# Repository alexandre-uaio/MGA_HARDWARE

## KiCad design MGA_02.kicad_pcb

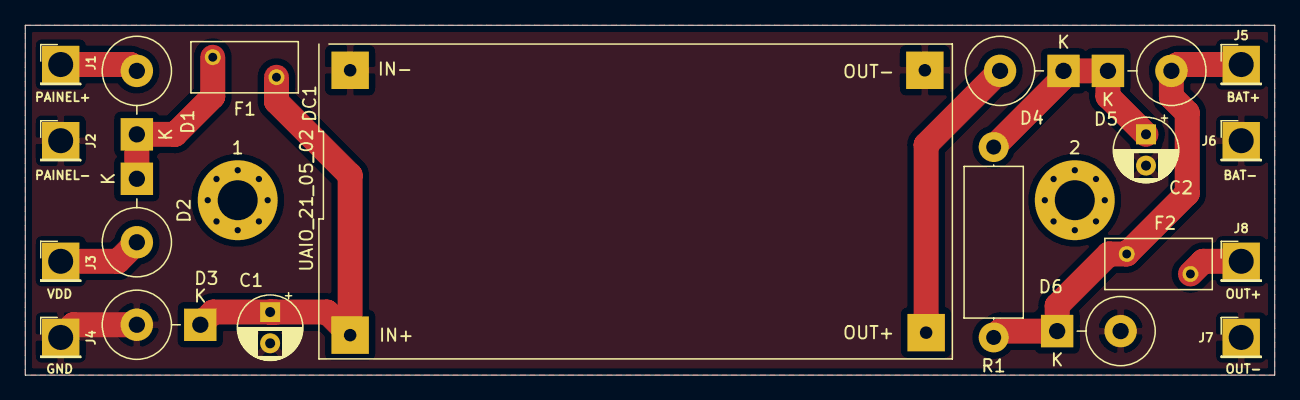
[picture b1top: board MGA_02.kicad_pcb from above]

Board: 2 copper layers, 100.0 x 28.0 mm, 22 parts (0 on the bottom side), 9 nets.

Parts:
1, 2: MountingHole_3.2mm_M3_Pad_Via
C1, C2: 100uFx50V; CP_Radial_D5.0mm_P2.50mm
D1, D2, D3, D4, D5, D6: UF5406; D_DO-201AE_P5.08mm_Vertical_KathodeUp
DC1: DC_DC_60V
F1, F2: Polyfuse; Fuse_BelFuse_0ZRE0005FF_L8.3mm_W3.8mm
J1: Painel +; PinHeader_1x01_F_2mm
J2: Painel -; PinHeader_1x01_F_2mm
J3: VDD; PinHeader_1x01_F_2mm
J4: GND; PinHeader_1x01_F_2mm
J5: BAT +; PinHeader_1x01_F_2mm
J6: BAT -; PinHeader_1x01_F_2mm
J7: OUT-; PinHeader_1x01_F_2mm
J8: OUT+; PinHeader_1x01_F_2mm
R1: 10R/3W; R_Axial_DIN0414_L11.9mm_D4.5mm_P15.24mm_Horizontal

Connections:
GND: C1.2, C2.2, D3.2, D6.2, DC1.2, DC1.4, J2.1, J4.1, J6.1, J7.1
unnamed: C1.1, D3.1, DC1.1, F1.1
unnamed: C2.1, D4.1, D5.1, R1.2
unnamed: D1.1, D2.1, F1.2
unnamed: D1.2, J1.1
unnamed: D2.2, J3.1
unnamed: D4.2, DC1.3
unnamed: D5.2, D6.1, F2.2, J5.1, R1.1
unnamed: F2.1, J8.1

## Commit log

2021-05-29 Criação repositorio Versão UAIO_21_05_02
2021-05-29 Correção do Conversor DC-DC
